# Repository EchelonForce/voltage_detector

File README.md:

# Eurorack Voltage Detector 

This is a design for a eurorack voltage detector.

Full writeup: https://www.robotdialogs.com/2023/01/eurorack-voltage-detector.html

This work is licensed under a Creative Commons Attribution-NonCommercial-ShareAlike 4.0 International License. https://creativecommons.org/licenses/by-nc-sa/4.0/

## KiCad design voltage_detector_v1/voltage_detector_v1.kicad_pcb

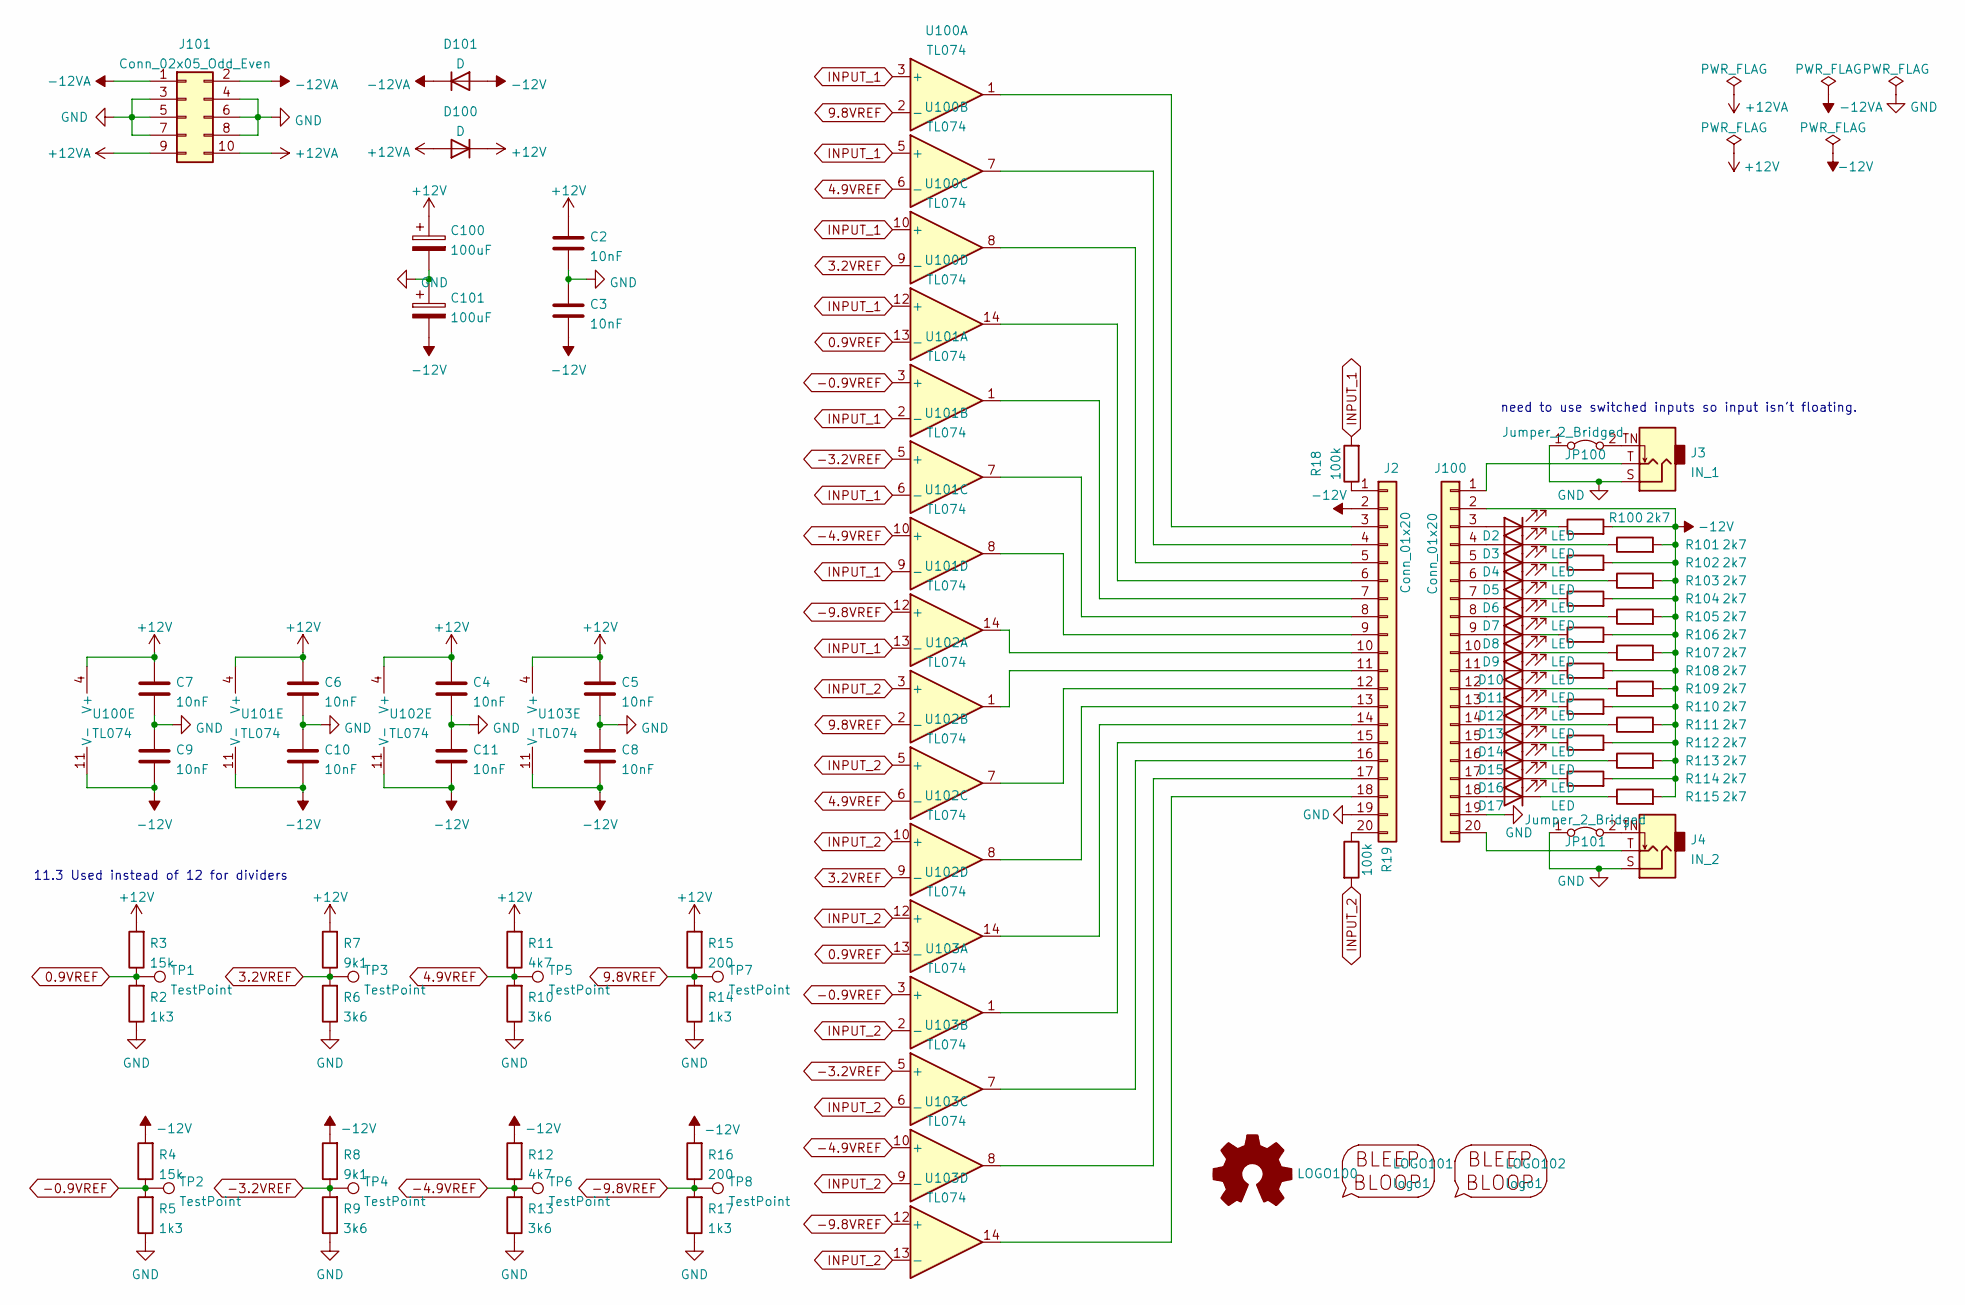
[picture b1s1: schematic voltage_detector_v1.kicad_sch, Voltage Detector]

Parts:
C2, C3, C4, C5, C6, C7, C8, C9, C10, C11: 10nF; C_1206_3216Metric_Pad1.33x1.80mm_HandSolder
C100, C101: 100uF; CP_Radial_D5.0mm_P2.50mm
D2, D3, D4, D5, D6, D7, D8, D9, D10, D11, D12, D13, D14, D15, D16, D17: LED; LED_D3.0mm
D100, D101: D; D_A-405_P2.54mm_Vertical_KathodeUp
J2: Conn_01x20; PinHeader_1x20_P2.54mm_Horizontal
J3: IN_1; Jack_3.5mm_MJ-355W_and_PJ398SM_Vertical
J4: IN_2; Jack_3.5mm_MJ-355W_and_PJ398SM_Vertical
J100: Conn_01x20; PinSocket_1x20_P2.54mm_Vertical
J101: Conn_02x05_Odd_Even; IDC-Header_2x05_P2.54mm_Vertical
JP100, JP101: Jumper_2_Bridged; SolderJumper-2_P1.3mm_Bridged_Pad1.0x1.5mm
LOGO100: Logo_Open_Hardware_Small; OSHW-Symbol_6.7x6mm_SilkScreen
LOGO101: logo1; Logo1
LOGO102: logo1; Logo2
R2, R5, R14, R17: 1k3; R_1206_3216Metric_Pad1.30x1.75mm_HandSolder
R3, R4: 15k; R_1206_3216Metric_Pad1.30x1.75mm_HandSolder
R6, R9, R10, R13: 3k6; R_1206_3216Metric_Pad1.30x1.75mm_HandSolder
R7, R8: 9k1; R_1206_3216Metric_Pad1.30x1.75mm_HandSolder
R11, R12: 4k7; R_1206_3216Metric_Pad1.30x1.75mm_HandSolder
R15, R16: 200; R_1206_3216Metric_Pad1.30x1.75mm_HandSolder
R18, R19: 100k; R_1206_3216Metric_Pad1.30x1.75mm_HandSolder
R100, R101, R102, R103, R104, R105, R106, R107, R108, R109, R110, R111, R112, R113, R114, R115: 2k7; R_1206_3216Metric_Pad1.30x1.75mm_HandSolder
TP1, TP2, TP3, TP4, TP5, TP6, TP7, TP8: TestPoint; TestPoint_Pad_D1.0mm_minimal
U100, U101, U102, U103: TL074; DIP-14_W7.62mm_Socket_LongPads

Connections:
0.9VREF: R2.2, R3.1, TP1.1, U100.13 (-), U102.13 (-)
3.2VREF: R6.2, R7.1, TP3.1, U100.9 (-), U102.9 (-)
4.9VREF: R10.2, R11.1, TP5.1, U100.6 (-), U102.6 (-)
9.8VREF: R14.2, R15.1, TP7.1, U100.2 (-), U102.2 (-)
+12V: C2.1, C4.1, C5.1, C6.1, C7.1, C100.1, D100.1 (K), R3.2, R7.2, R11.2, R15.2, U100.4 (V+), U101.4 (V+), U102.4 (V+), U103.4 (V+)
+12VA: D100.2 (A), J101.9, J101.10
-0.9VREF: R4.1, R5.2, TP2.1, U101.3 (+), U103.3 (+)
-3.2VREF: R8.1, R9.2, TP4.1, U101.5 (+), U103.5 (+)
-4.9VREF: R12.1, R13.2, TP6.1, U101.10 (+), U103.10 (+)
-9.8VREF: R16.1, R17.2, TP8.1, U101.12 (+), U103.12 (+)
-12V: C3.2, C8.2, C9.2, C10.2, C11.2, C101.2, D101.2 (A), J2.2, J100.2, R4.2, R8.2, R12.2, R16.2, R100.2, R101.2, R102.2, R103.2, R104.2, R105.2, R106.2, R107.2, R108.2, R109.2, R110.2, R111.2, R112.2, R113.2, R114.2, R115.2, U100.11 (V-), U101.11 (V-), U102.11 (V-), U103.11 (V-)
-12VA: D101.1 (K), J101.1, J101.2
GND: C2.2, C3.1, C4.2, C5.2, C6.2, C7.2, C8.1, C9.1, C10.1, C11.1, C100.2, C101.1, J2.19, J3.S, J4.S, J100.19, J101.3, J101.4, J101.5, J101.6, J101.7, J101.8, JP100.1 (A), JP101.1 (A), R2.1, R5.1, R6.1, R9.1, R10.1, R13.1, R14.1, R17.1
INPUT_1: R18.2, U100.3 (+), U100.5 (+), U100.10 (+), U100.12 (+), U101.2 (-), U101.6 (-), U101.9 (-), U101.13 (-)
INPUT_2: R19.2, U102.3 (+), U102.5 (+), U102.10 (+), U102.12 (+), U103.2 (-), U103.6 (-), U103.9 (-), U103.13 (-)
unnamed: D2.1 (K), R100.1
unnamed: D2.2 (A), J100.3
unnamed: D3.1 (K), R101.1
unnamed: D3.2 (A), J100.4
unnamed: D4.1 (K), R102.1
unnamed: D4.2 (A), J100.5
unnamed: D5.1 (K), R103.1
unnamed: D5.2 (A), J100.6
unnamed: D6.1 (K), R104.1
unnamed: D6.2 (A), J100.7
unnamed: D7.1 (K), R105.1
unnamed: D7.2 (A), J100.8
unnamed: D8.1 (K), R106.1
unnamed: D8.2 (A), J100.9
unnamed: D9.1 (K), R107.1
unnamed: D9.2 (A), J100.10
unnamed: D10.1 (K), R108.1
unnamed: D10.2 (A), J100.11
unnamed: D11.1 (K), R109.1
unnamed: D11.2 (A), J100.12
unnamed: D12.1 (K), R110.1
unnamed: D12.2 (A), J100.13
unnamed: D13.1 (K), R111.1
unnamed: D13.2 (A), J100.14
unnamed: D14.1 (K), R112.1
unnamed: D14.2 (A), J100.15
unnamed: D15.1 (K), R113.1
unnamed: D15.2 (A), J100.16
unnamed: D16.1 (K), R114.1
unnamed: D16.2 (A), J100.17
unnamed: D17.1 (K), R115.1
unnamed: D17.2 (A), J100.18
unnamed: J2.1, R18.1
unnamed: J2.3, U100.1
unnamed: J2.4, U100.7
unnamed: J2.5, U100.8
unnamed: J2.6, U100.14
unnamed: J2.7, U101.1
unnamed: J2.8, U101.7
unnamed: J2.9, U101.8
unnamed: J2.10, U101.14
unnamed: J2.11, U102.1
unnamed: J2.12, U102.7
unnamed: J2.13, U102.8
unnamed: J2.14, U102.14
unnamed: J2.15, U103.1
unnamed: J2.16, U103.7
unnamed: J2.17, U103.8
unnamed: J2.18, U103.14
unnamed: J2.20, R19.1
unnamed: J3.T, J100.1
unnamed: J3.TN, JP100.2 (B)
unnamed: J4.TN, JP101.2 (B)
unnamed: J4.T, J100.20

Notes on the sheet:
11.3 Used instead of 12 for dividers
need to use switched inputs so input isn't floating.

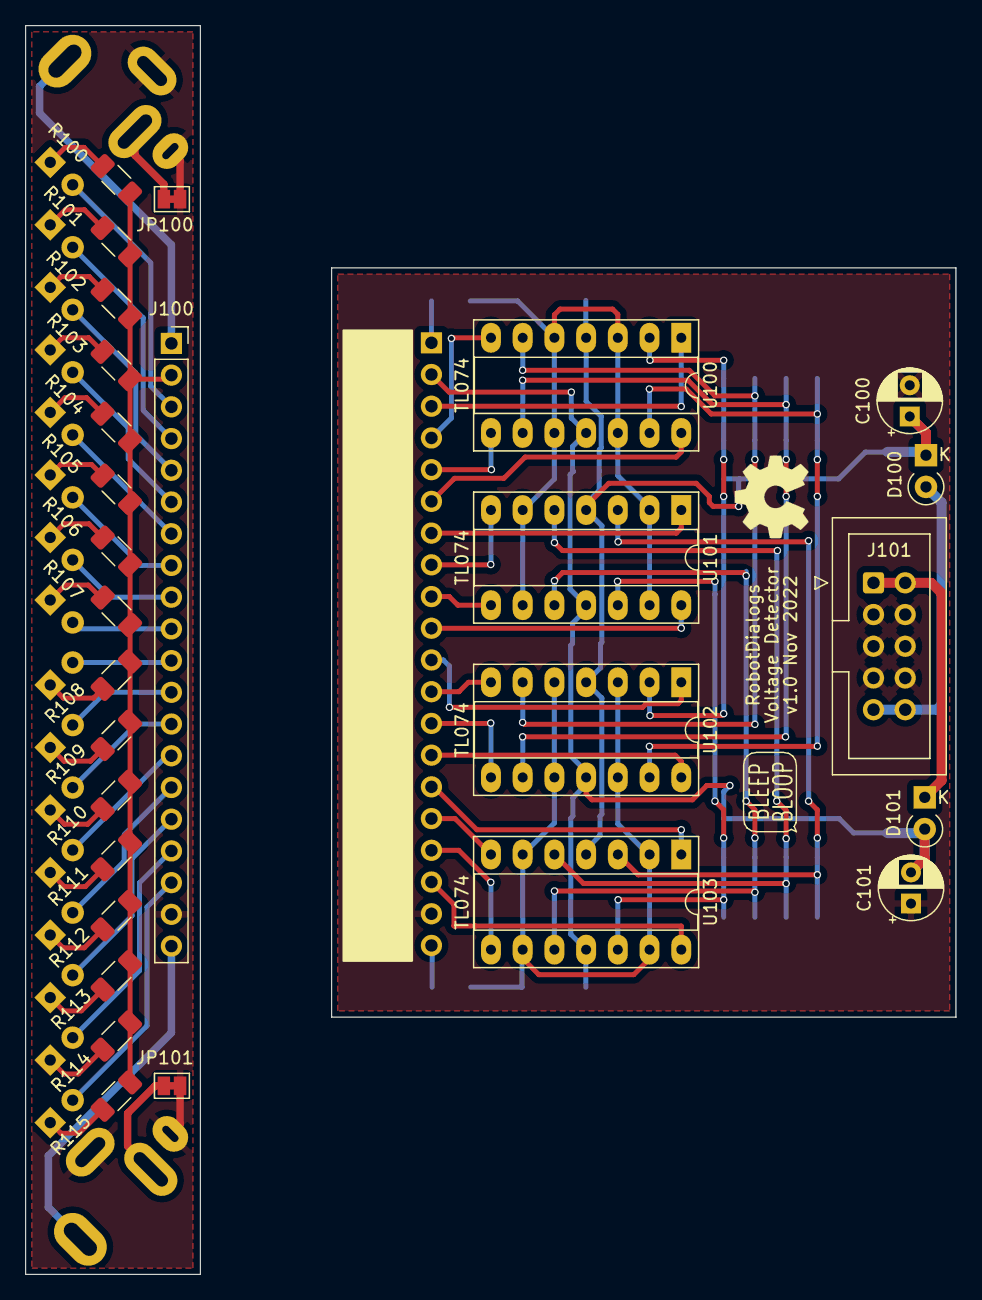
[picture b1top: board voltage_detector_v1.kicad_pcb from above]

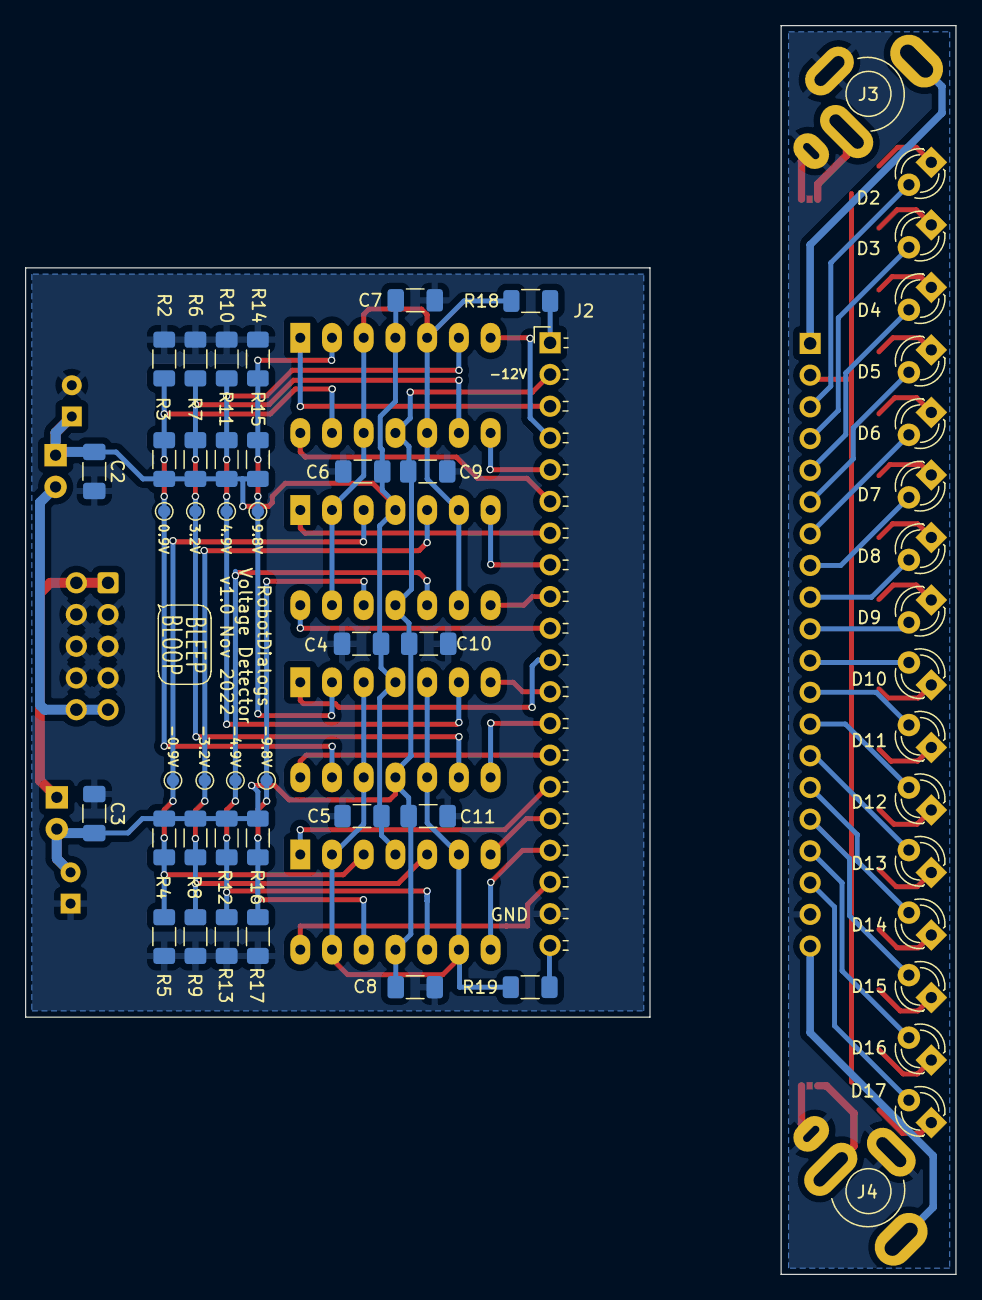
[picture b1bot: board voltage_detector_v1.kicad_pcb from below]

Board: 2 copper layers, 74.5 x 100.0 mm, 86 parts (55 on the bottom side), 69 nets.

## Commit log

2022-12-04 Initial commit with gitignore
2022-12-11 Schematic and PCB routing
2022-12-11 Panelized v1
2023-01-18 Schematic v1 pdf
2023-01-18 Front Panel v1
2023-01-18 Readme updated
